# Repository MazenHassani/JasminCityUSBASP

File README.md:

# JasminCityUSBASP
USBASP AVR Programmer
based on famous Thomas Fischl's USBASP Atmel AVR controllers programmer (www.fischl.de/usbasp)
re-designed by me with help from Lilypad Arduino Simple board design

3D Visualization using 3dbrdviewer.cytec.bg/

TOP :

Bottom:

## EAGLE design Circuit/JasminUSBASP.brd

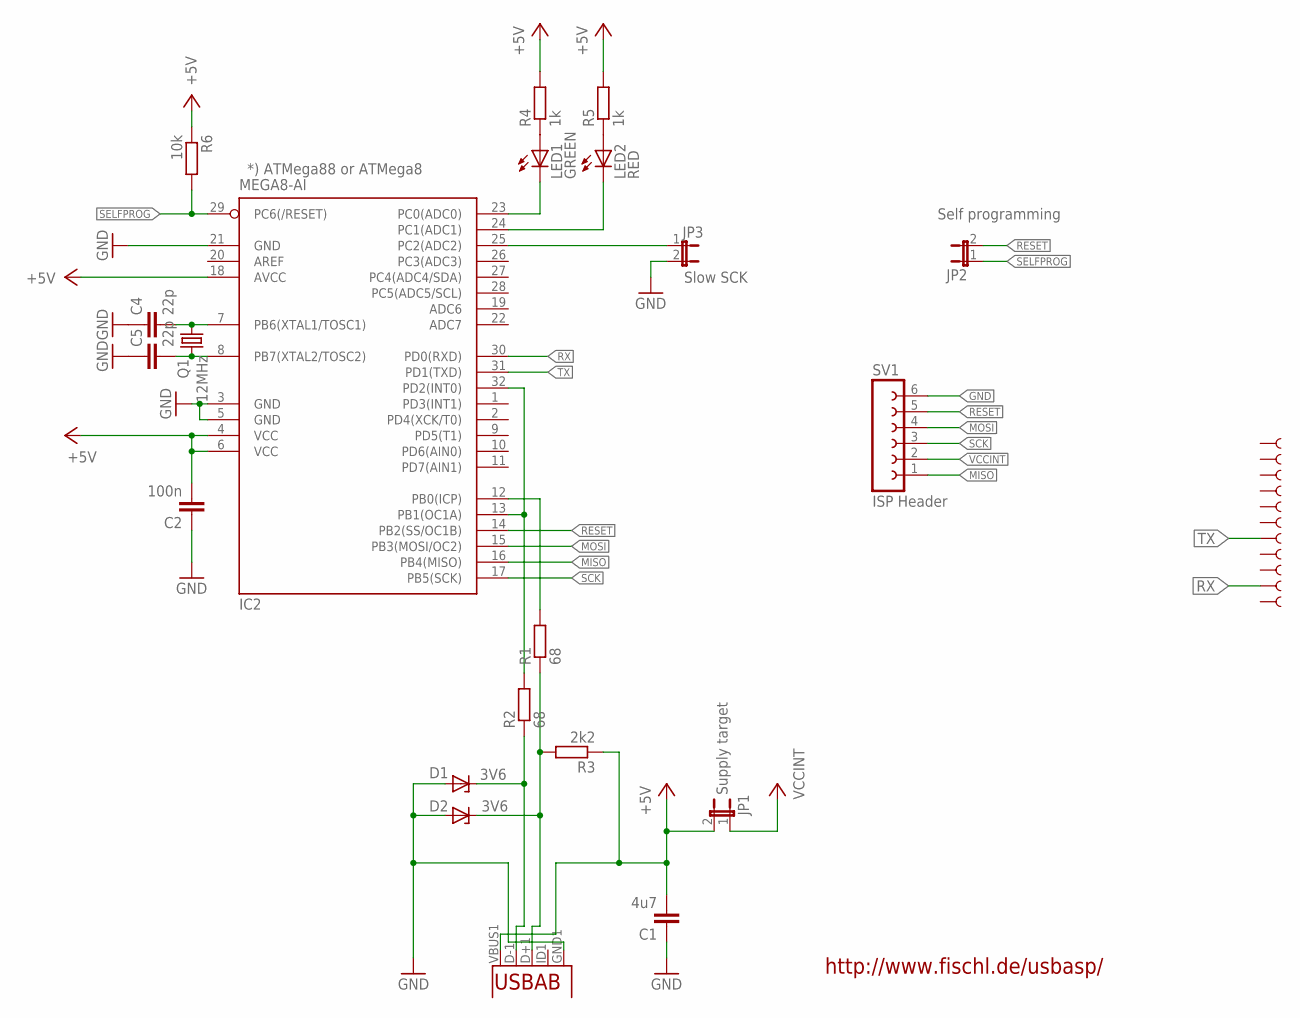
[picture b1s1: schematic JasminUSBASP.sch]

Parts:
A2/16, A3/17, A4/18, A5/19: SEWTAP9; PETAL-LONG-1-2SIDE
C1: 4u7; C1206
C2: 100n; C1206
C4, C5: 22p; C1206
D1, D2: 3V6; DO34Z7
IC2: MEGA8-AI; TQFP32-08
JP1: Supply target; JP1
JP2: Self programming; JP1
JP3: Slow SCK; JP1
JP9: Micro USB; USB-AB-MICRO-SMD_V03
LED1: GREEN; CHIPLED_1206
LED2: RED; CHIPLED_1206
Q1: 12MHz; HC49/S
R1, R2: 68; R1206
R3: 2k2; R1206
R4, R5: 1k; R1206
R6: 10k; R1206
SV1: ISP Header; FE06W
U$4, U$35, U$37, U$39, U$41, U$43, U$45: SEWTAP9; PETAL-LONG-1-2SIDE

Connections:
+5V: C1.2, C2.2, IC2.4 (VCC), IC2.6 (VCC), IC2.18 (AVCC), JP1.2, JP9.VBUS1 (VBUS), R3.1, R4.2, R5.2, R6.1
GND: C1.1, C2.1, C4.1, C5.1, D1.A, D2.A, IC2.3 (GND), IC2.5 (GND), IC2.21 (GND), JP3.2, JP9.GND1 (GND), SV1.6
MISO: IC2.16 (PB4(MISO)), SV1.1
MOSI: IC2.15 (PB3(MOSI/OC2)), SV1.4
unnamed: LED1.A, R4.1
unnamed: LED2.A, R5.1
unnamed: D2.C, JP9.D+1 (D+), R1.1, R3.2
unnamed: IC2.13 (PB1(OC1A)), IC2.32 (PD2(INT0)), R2.2
unnamed: D1.C, JP9.D-1 (D-), R2.1
unnamed: IC2.25 (PC2(ADC2)), JP3.1
unnamed: IC2.23 (PC0(ADC0)), LED1.C
unnamed: IC2.24 (PC1(ADC1)), LED2.C
unnamed: IC2.12 (PB0(ICP)), R1.2
unnamed: C4.2, IC2.7 (PB6(XTAL1/TOSC1)), Q1.2
unnamed: C5.2, IC2.8 (PB7(XTAL2/TOSC2)), Q1.1
RESET: IC2.14 (PB2(SS/OC1B)), JP2.2, SV1.5
RX: IC2.30 (PD0(RXD)), U$39.1
SCK: IC2.17 (PB5(SCK)), SV1.3
SELFPROG: IC2.29 (PC6(/RESET)), JP2.1, R6.2
TX: IC2.31 (PD1(TXD)), U$41.1
VCCINT: JP1.1, SV1.2

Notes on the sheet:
http://www.fischl.de/usbasp/
*) ATMega88 or ATMega8

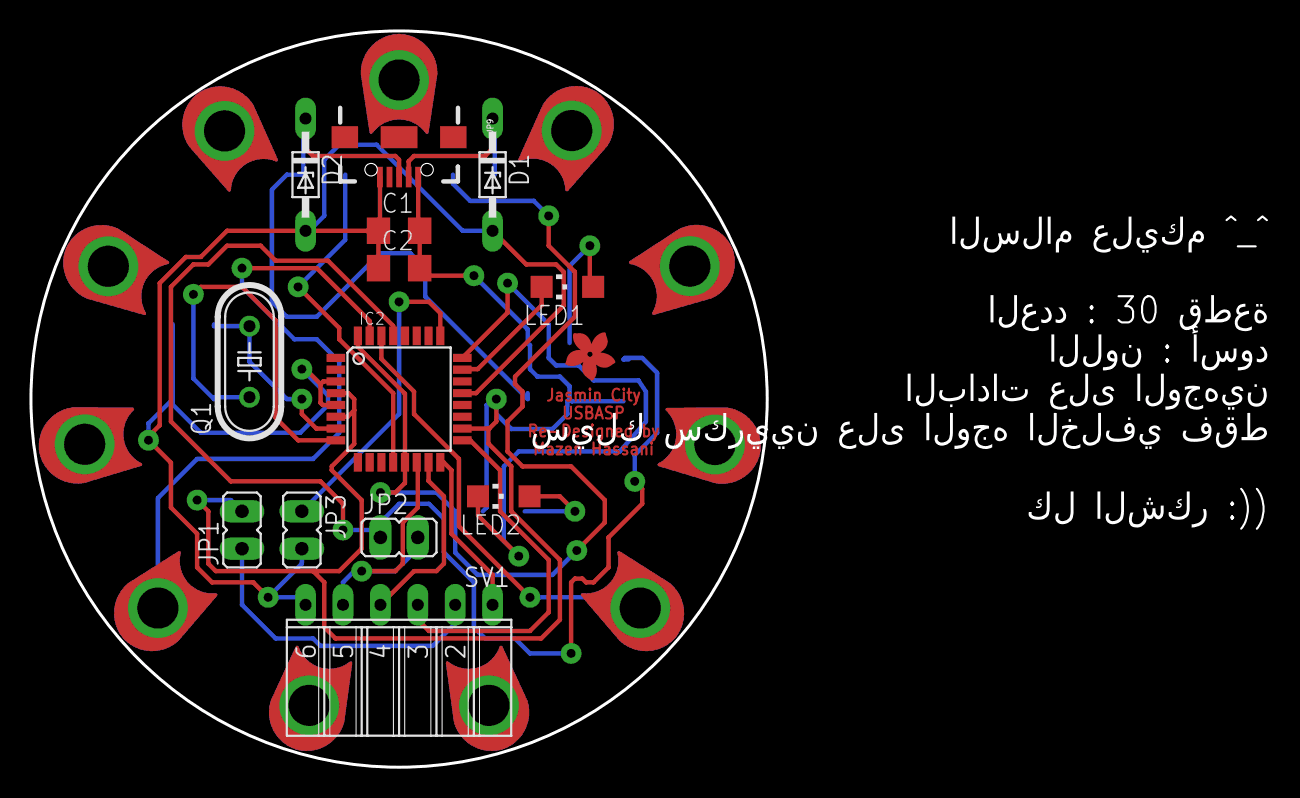
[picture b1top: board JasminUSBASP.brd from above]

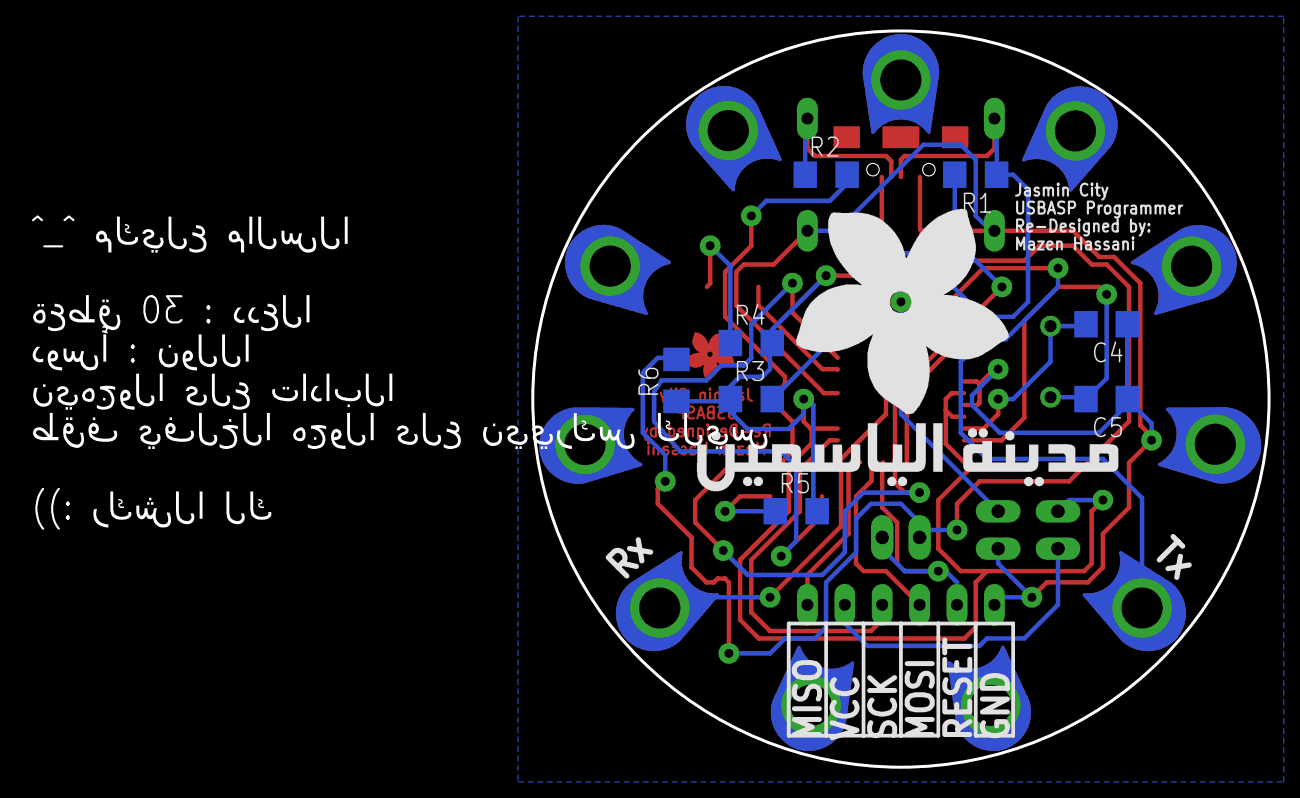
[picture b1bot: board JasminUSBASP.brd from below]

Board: 2 copper layers, 84.1 x 50.0 mm, 34 parts (9 on the bottom side), 21 nets.

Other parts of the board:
U$1: JASMIN_CITY
U$2: JASMIN_1/4

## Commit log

2017-03-21 Add files via upload
    3D Visualization
2017-03-21 Add files via upload
    EAGLE Design
2017-03-22 Add files via upload
    using SketchUp 17.1.174
2017-03-22 Update README.md
    add image
2017-03-22 Update README.md
    add images
2017-03-22 Update README.md
    add references and mentions

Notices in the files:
parts and their libraries:
SparkFun-Connectors: Licensing: Creative Commons ShareAlike 4.0 International - https://creativecommons.org/licenses/by-sa/4.0
